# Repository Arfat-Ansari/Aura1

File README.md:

# AURA 1 - Autonomous Desktop Companion Robot

Author: Arfat Ansari
Target: Maker Faire Shenzhen 2026 / Hack Club Fallen

This is AURA 1, my autonomous companion robot project. I am building this because I wanted an animatronic companion sitting on my desk that actually feels responsive and alive when I am working or talking, instead of just sitting there like a static piece of plastic.

Most commercial desktop robots either cost hundreds of dollars or their neck movements look so jerky and robotic like a toy servo snapping around. My goal with AURA 1 is to build an open hardware companion robot with smooth organic motion, expressive circular color screens, real time laser distance sensing, and sound reactivity, all running on an ESP32-S3 microcontroller.

## What It Does

- 3-DOF Kinematic Head: The head moves in 3 axes (pan left/right, pitch up/down, roll tilt sideways) driven by three TowerPro MG90S metal gear servos linked with carbon fiber pushrods and brass ball joints on a central 608ZZ bearing turntable.
- Capacitive Petting and Purr: A capacitive touch zone across the skull top detects human hand petting. When stroked, the servos do a subtle 25Hz haptic purr vibration, the eyes squint into happy anime arches, and the neck halo glows warm amber.
- Dual Round Color Eyes: Two GC9A01 1.28 inch 240x240 circular IPS LCD screens running at 60 FPS over dual SPI channels. The eyes have animated pupils that dilate, blink, and track movement with natural saccades.
- Laser Distance Perception: An ST VL53L1X time-of-flight laser distance sensor on the forehead reads ranges up to 4 meters, so the robot knows when someone is sitting in front of it and turns to look at them.
- Sound Reactive: An INMP441 I2S digital MEMS microphone streams audio over DMA with real time FFT beat detection, allowing the robot to nod or react to music and voices.
- Emotion Halo: A 12-LED WS2812B RGB halo ring around the neck turntable gives ambient emotional color feedback.
- Custom Power Stage: High efficiency Silergy SY8089 synchronous step-down buck converter stepping 5V down to a stable 3.3V logic rail with under 2mV ripple, paired with a 470uF low-ESR bulk reservoir capacitor and Schottky diode isolation so servo stall current spikes never drop the logic rail or reset the microcontroller.

## Project Structure

```text
Aura1/
  cad/
    aura_base_chassis_printready.stl      # Base chassis with PCB standoffs and inspection cutout
    aura_skull_head_printready.stl        # Head skull frame with eye recesses and ToF mount
    aura_servo_bracket_printready.stl     # Internal neck servo mounting plate with M2 screw bosses
    aura_turntable_bearing_printready.stl # 608ZZ bearing turntable with central wire pass-through
    aura_face_visor_printready.stl        # Magnetic front face visor cowling with 4x magnet pockets
    aura_skull_cap_printready.stl         # Upper skull dome cap with touch pad mount and rear vents
    aura_halo_diffuser_printready.stl     # Neck turntable halo light optical diffuser ring
    aura_torso_cowl_printready.stl        # Torso mid-body cosmetic enclosure jacket with cooling louvers
    aura_cable_guides_printready.stl      # Turntable neck cable harness guide and strain relief sleeve
    aura_desk_stand_printready.stl        # Anti-vibration desktop weighted docking stand with acoustic cutout
    aura_battery_door_printready.stl      # Quick-release magnetic battery service hatch door
    aura_assembly.blend                   # Full Blender 4.2 parametric 3D CAD assembly
  hardware/
    circuit_architecture.md               # Complete electrical power and PCB design specification
    pcb/
      aura_carrier_board.kicad_pcb        # Production KiCad 2-layer carrier board layout (0 DRC)
      aura_carrier_board.epro             # EasyEDA Pro project file
      aura_pcb_populated_3d.blend         # Populated 3D carrier motherboard Blender CAD model
      jlcpcb_bom.csv                      # SMT manufacturing BOM with LCSC part numbers
      jlcpcb_cpl.csv                      # SMT Pick-and-Place component centroid coordinates
      aura_pcb_layout_2d.png              # 2D PCB layout blueprint
      drc_report_final.txt                # Zero DRC verification report
    schematics/
      aura_schematic_full.png             # Complete system circuit schematic diagram
  firmware/
    platformio.ini                        # PlatformIO configuration for ESP32-S3
    include/
      servo_smooth.h                    # Cubic easing servo motion engine
      display_eyes.h                    # Dual GC9A01 60 FPS eye rendering and saccades
      kinematics.h                      # 3-DOF spherical pushrod kinematics math
      emotion_engine.h                  # State machine for idle, alert, and tracking behaviors
      petting_purr.h                    # Capacitive touch filtering and 25Hz purr vibration
      sensors.h                         # VL53L1X ToF, touch, and microphone polling
      halo_leds.h                       # 12-LED WS2812B RGB halo animations
      audio_dsp.h                       # INMP441 I2S microphone sampling and FFT
      gesture_engine.h                  # ST VL53L1X multi-zone optical gesture and peek-a-boo
      power_mgr.h                       # 18650 Li-ion battery ADC monitoring and power states
      behavior_engine.h                 # Autonomous desktop personality and sleep/wake engine
      exploration_engine.h              # Autonomous environmental exploration and ambient gaze engine
      espnow_mesh.h                     # Multi-robot ESP-NOW peer handshake and swarm interaction
      web_dashboard.h                   # Wireless SoftAP telemetry and calibration dashboard
      sleep_manager.h                   # Deep-sleep power optimization and sub-12mA wake stubs
    src/
      main.cpp                          # Dual-core FreeRTOS main loop and task scheduler
  images/
    aura_day20_1_color_sleep_mode_showcase.png # AURA-1 in quiescent deep-sleep standby with dimmed halo and drooped head pose
    aura_day20_2_color_battery_door_closeup.png # Undercarriage macro closeup of magnetic quick-release battery service door
    aura_day20_3_color_wake_stub_reaction.png # Instantaneous capacitive wake event transitioning companion to active tracking
    aura_day20_4_design_battery_door_wireframe.png # Technical orthographic wireframe of battery hatch showing N52 magnet pockets and hinge tabs
    aura_day20_5_design_deep_sleep_power_cutaway.png # Section cutaway highlighting power rail gating and RTC controller domains
    aura_day20_6_design_exploded_battery_chassis_iso.png # Exploded CAD view of 18650 cell, EVA foam pad, magnetic door, and chassis floor
    aura_day19_1_color_multi_robot_showcase.png # Dual AURA-1 robots interacting over low-latency ESP-NOW peer mesh
    aura_day19_2_color_desk_stand_closeup.png # Macro beauty closeup of weighted desktop docking stand
    aura_day19_3_color_peer_sync_halo_pose.png # Robot responding to peer social greeting with electric violet halo
    aura_day19_4_design_desk_stand_wireframe.png # CAD technical elevation showing acoustic notch and ballast cavity
    aura_day19_5_design_peer_rf_architecture.png # CAD cutaway view of ESP32-S3 inverted-F antenna RF clearance
    aura_day19_6_design_exploded_stand_chassis_iso.png # Exploded CAD view of silicone pads, stand, and chassis
    aura_day18_1_color_exploration_showcase.png # Robot in active inquisitive environmental exploration pose
    aura_day18_2_color_cable_guide_closeup.png # Macro beauty closeup of turntable cable guide sleeve
    aura_day18_3_color_ambient_tracking_pose.png # Robot adapting to room lighting with wide curious gaze
    aura_day18_4_design_cable_guide_wireframe.png # CAD technical elevation of cable guide bellmouth and flange
    aura_day18_5_design_neck_wiring_cutaway.png # CAD cutaway showing wire harness protected inside 608ZZ bore
    aura_day18_6_design_exploded_neck_assembly.png # Exploded CAD view of base, bearing, guide sleeve, turntable
    aura_day17_1_color_dualcore_showcase.png # Full robot in active dual-core FreeRTOS multitasking pose
    aura_day17_2_color_torso_cowl_closeup.png # Macro closeup of torso mid-body cowl and cooling louvers
    aura_day17_3_color_freertos_task_telemetry.png # Robot next to telemetry monitor showing Core 0 and Core 1 load
    aura_day17_4_design_torso_cowl_wireframe.png # CAD technical elevation view of torso cowl geometry
    aura_day17_5_design_dualcore_task_architecture.png # CAD cutaway view showing internal dual-core carrier PCB
    aura_day17_6_design_exploded_torso_assembly.png # Exploded CAD view of torso chassis, cowl, diffuser, turntable
    aura_day16_1_color_halo_diffuser_showcase.png # Full robot with frosted halo diffuser glowing neon cyan
    aura_day16_2_color_dashboard_phone_view.png # Macro beauty shot of robot on desk next to phone UI
    aura_day16_3_color_live_trim_pose.png       # Robot responding to wireless calibration with purple aura
    aura_day16_4_design_diffuser_ring_wireframe.png # CAD elevation & optical wall thickness of diffuser ring
    aura_day16_5_design_neck_turntable_diffuser_cutaway.png # CAD cutaway showing LED ring inside channel
    aura_day16_6_design_exploded_chassis_diffuser_iso.png # Exploded CAD view of base, ring, diffuser, bearing
    aura_day15_1_color_petting_purr_showcase.png # Full robot in happy petting state with amber glow
    aura_day15_2_color_skull_dome_rear_iso.png  # Color 3/4 rear isometric view of skull dome & vents
    aura_day15_3_color_head_complete_assembly.png # Beauty perspective shot of fully enclosed head
    aura_day15_4_design_skull_cap_wireframe.png # CAD top elevation & curvature analysis of skull dome
    aura_day15_5_design_touch_pad_cutaway.png   # CAD cutaway showing internal capacitive copper sensor
    aura_day15_6_design_head_snap_fit_iso.png   # CAD exploded view of 4x snap tabs and skull interface
    aura_day14_1_color_visor_showcase.png       # Full finished robot showcase with magnetic visor
    aura_day14_2_color_visor_detachment.png     # Perspective view showing magnetic snap pins and modularity
    aura_day14_3_color_deep_sleep_pose.png      # Color render of autonomous deep sleep pose with drooped head
    aura_day14_4_design_visor_front_wireframe.png # CAD front engineering layout of bezels and apertures
    aura_day14_5_design_magnet_pockets_iso.png  # CAD rear view of visor magnet pockets and locating pins
    aura_day14_6_design_exploded_head_assembly.png # CAD exploded view of skull, screens, magnets, and visor
    aura_day13_1_color_untethered_showcase.png  # Full untethered cordless robot showcase render
    aura_day13_2_color_usbc_rear_closeup.png    # Macro closeup of rear USB-C charging port and power switch
    aura_day13_3_color_low_battery_reaction.png # Color render of low-battery tired eye droop and amber warning
    aura_day13_4_design_battery_cradle_cutaway.png # CAD cutaway showing 18650 cell in cradle and TP4056
    aura_day13_5_design_power_stage_layout.png  # Top-down CAD engineering view of complete power stage layout
    aura_day13_6_design_rear_port_iso.png       # Isometric CAD view of rear chassis skirt and ports
    aura_day12_1_color_gesture_showcase.png     # Full robot interactive optical gesture showcase render
    aura_day12_2_color_optical_baffle_closeup.png # Macro closeup of forehead optical ToF sensor and septum
    aura_day12_3_design_optical_cutaway.png     # CAD cutaway showing internal VL53L1X board and gasket
    aura_day12_4_design_multizone_geometry.png  # Front engineering CAD view showing multi-zone optical geometry
    aura_day12_5_color_peekaboo_reaction.png    # Color render showing shy peek-a-boo interaction pose
    aura_day12_6_design_optical_module_iso.png  # CAD isometric engineering view of forehead optical module
    aura_day11_1_color_spatial_tracking.png     # Full showcase render with spatial sound tracking pose
    aura_day11_2_color_mic_port_closeup.png     # Macro closeup of stereo acoustic mic port on visor
    aura_day11_3_design_stereo_mic_cutaway.png  # CAD cutaway showing internal INMP441 board and gasket
    aura_day11_4_design_spatial_acoustic_baseline.png # Front engineering CAD view of 80mm acoustic baseline
    aura_day10_full_showcase.png          # Day 10 full robot showcase render with acoustic speaker grill
    aura_day10_speaker_closeup.png        # Day 10 macro view of 9-slot acoustic sound grill
    aura_day10_cad_acoustic_cavity.png    # Day 10 CAD cutaway showing internal 28mm speaker pocket
    aura_day10_cad_max98357a_mount.png    # Day 10 CAD view of MAX98357A amplifier floor standoffs
    aura_day9_full_showcase.png           # Full 3/4 showcase render in happy resting pose
    aura_day9_petting_amber_glow.png      # Warm amber halo glow during petting reaction
    aura_day9_head_touchpad_closeup.png   # Close-up of head touch zone and happy eye displays
    aura_day9_turntable_assembly.png      # Technical view of 608ZZ bearing turntable
    aura_day9_purr_kinematics.png         # Frontal view showing neck tilt and purr flutter
    aura_day8_full_showcase.png           # Day 8 full showcase render
    aura_day8_eye_closeup.png             # Day 8 eye closeup
    aura_day8_internal_bracket.png        # Day 8 internal servo bracket
  .gitignore
  README.md
```

## Hardware and Components

1. Microcontroller: ESP32-S3-WROOM-1-N16R8 (Xtensa Dual-Core 240MHz, 16MB Flash, 8MB PSRAM)
2. Displays: 2x GC9A01 1.28 inch 240x240 Round IPS LCD Modules (SPI)
3. Actuators: 3x TowerPro MG90S Metal Gear Micro Servos (1x Pan, 2x Differential Tilt)
4. Bearing: 1x 608ZZ Radial Ball Bearing (8mm ID, 22mm OD, 7mm Height)
5. Linkages: 2x 2.0mm Carbon Fiber Pushrods with M2 Brass Ball Joints
6. Distance Sensor: ST VL53L1X Time-of-Flight Laser Sensor (I2C)
7. Audio: TDK InvenSense INMP441 Omnidirectional Digital I2S MEMS Microphone
8. Emotion Lighting: 12x WS2812B 5050 Addressable RGB LEDs
9. Power Converter: Silergy SY8089 2A 1.5MHz Synchronous Step-Down Buck Converter (5V to 3.3V)
10. Capacitors: 470uF 16V Low-ESR Bulk Electrolytic + 2x 22uF X5R Ceramic Smoothing
11. Hardware: M3 Brass Threaded Inserts, M3 Brass Hex Standoffs, M2 Mounting Screws

## Pinout and Wiring

ESP32-S3 GPIO mapping for the carrier board:

| Function | GPIO Pin | Bus / Protocol | Notes |
|---|---|---|---|
| Servo Pan | GPIO 4 | LEDC PWM Ch0 | Base horizontal turntable |
| Servo Tilt Left | GPIO 5 | LEDC PWM Ch1 | Left pushrod actuator |
| Servo Tilt Right | GPIO 6 | LEDC PWM Ch2 | Right pushrod actuator |
| Left Eye MOSI | GPIO 11 | SPI2 (FSPI) | Shared SPI data line |
| Left Eye SCLK | GPIO 12 | SPI2 (FSPI) | Shared SPI clock line |
| Left Eye CS | GPIO 13 | GPIO Out | Chip select left display |
| Right Eye CS | GPIO 14 | GPIO Out | Chip select right display |
| Display DC | GPIO 9 | GPIO Out | Shared Data/Command select |
| Display RST | GPIO 10 | GPIO Out | Shared Hardware reset |
| Display Backlight | GPIO 21 | LEDC PWM Ch3 | 2N7002 MOSFET brightness control |
| I2C SDA (Sensors) | GPIO 47 | I2C Bus | 4.7k pull-up to 3.3V |
| I2C SCL (Sensors) | GPIO 48 | I2C Bus | 4.7k pull-up to 3.3V |
| VL53L1X XSHUT | GPIO 2 | GPIO Out | Sensor hardware enable |
| VL53L1X INT | GPIO 18 | GPIO Interrupt | New measurement alert |
| I2S Mic SCK (Clock) | GPIO 40 | I2S Audio In | Shared bit clock for dual INMP441 mics |
| I2S Mic WS (L/R) | GPIO 38 | I2S Audio In | Shared word select line |
| I2S Mic SD (Data) | GPIO 39 | I2S Audio In | Time-multiplexed stereo I2S data in |
| Mic Left L/R Pin | GND | Hardware Tie | Configures left mic to left I2S slot |
| Mic Right L/R Pin | 3.3V | Hardware Tie | Configures right mic to right I2S slot |
| RGB Halo Ring | GPIO 48 | RMT Peripheral | WS2812B 800kHz single-wire data |
| Touch Head Petting | GPIO 1 | Capacitive Touch | Touch 1 sensing through skull |
| I2S Speaker BCLK | GPIO 42 | I2S Audio Out | Bit clock line to MAX98357A amplifier |
| I2S Speaker LRCLK | GPIO 41 | I2S Audio Out | Word select line to MAX98357A amplifier |
| I2S Speaker DIN | GPIO 21 | I2S Audio Out | Serial PCM audio data to MAX98357A amplifier |
| Battery Voltage Sense | GPIO 3 | ADC1_CH2 | 100k/100k precision voltage divider (2.0x ratio) |
| TP4056 Charge Status | GPIO 8 | GPIO In | Active-low charging indicator from TP4056 STAT |

## Voice and Acoustic Subsystem

AURA 1 features a fully procedural voice engine and dedicated hardware acoustic subsystem:

1. Acoustic Hardware Enclosure:
   - 28mm 4-ohm 3W micro-speaker mounted with a 20-degree forward tilt toward the desktop surface.
   - 9-slot radial acoustic sound grill cut into the lower front perimeter of the base chassis to project sound outward without muffling.
   - Enclosed resonance chamber baffle providing back-volume isolation to eliminate acoustic phase cancellation and preserve warm low-mid harmonics.
   - Dedicated chassis floor boss mounting for a MAX98357A I2S Class D mono amplifier breakout board right beside the main circular carrier PCB.

2. Procedural Speech Synthesis (firmware/include/voice_synth.h):
   - Generates responsive robotic vocalizations in real time directly on the ESP32-S3 using mathematical frequency sweeps, harmonic overtone mixing, and ADSR amplitude envelopes.
   - Sound categories:
     * Happy Chirp: Ascending Wall-E style cheerful arpeggio trill with 22Hz vibrato.
     * Curious Trill: Inquisitive rising inflection for when objects are detected nearby.
     * Purr Warble: Warm 25Hz amplitude-modulated harmonic drone synced with physical servo petting.
     * Startled Squeak: Fast exponential downward drop for sudden loud noises or table impacts.
     * Confirm Chime: Clean two-tone musical bell (C6 to G6) acknowledging voice input.
     * Sleep Sigh: Slow descending filtered sine breath when the robot drifts to sleep.
   - Zero SD-card overhead: All audio is synthesized algorithmically in RAM and streamed over I2S DMA buffers.

3. Audio-Reactive Expressions:
   - Real-time amplitude envelope tracking (`getAudioLevel()`) and pitch detection (`getPitchRatio()`).
   - The dual GC9A01 eye displays dynamically squash and lift on high vocal notes.
   - The 12-LED neck halo ring flares in brightness synchronously with robot vocal volume.

## 3D Printing

All main structural parts are in the cad directory and ready to slice:

1. Base Chassis (`aura_base_chassis_printready.stl`):
   - Material: PETG (recommended for strength around the bearing pocket)
   - Layer height: 0.20mm
   - Perimeters: 3 or 4 walls
   - Infill: 25% gyroid
   - Note: Features 9 precision acoustic sound slots on the lower front skirt, an internal 28mm speaker pocket with sealing gasket ridge, mounting standoffs for the MAX98357A amplifier, a horizontal 18650 Li-ion battery retaining cradle with snap-fit ribs, rear USB-C charging receptacle cutout, power slide switch pocket, and 4x M3 PCB standoffs matching EasyEDA coordinates (64.0mm x 48.0mm).

## Battery Power and Charging Subsystem

AURA 1 is completely untethered and cordless, powered by an internal rechargeable lithium-ion power stage:

1. 18650 Battery Cell and Retention:
   - Houses a standard 18650 3.7V 3000mAh cylindrical Li-ion cell seated horizontally across the center-rear floor of the base chassis.
   - The chassis floor features molded semi-circular cradle ribs and flexible snap-fit retention clips to secure the cell against high-velocity head pan inertia without rattling.
   - A dedicated rear skirt aperture accommodates a flush USB-C charging port and miniature SPDT slide power switch.

2. Charge Management and Power Architecture:
   - TP4056 1A constant-current / constant-voltage (CC/CV) lithium charge management IC with internal thermal regulation and automatic recharge threshold.
   - Powers the high-efficiency Silergy SY8089 synchronous step-down buck converter to step battery voltage (3.2V - 4.2V) to a stable 3.3V logic rail.
   - Dedicated 470uF low-ESR bulk reservoir capacitor absorbs dynamic current spikes drawn by the three metal-gear servos so the ESP32-S3 microcontroller never experiences brownout resets.

3. Voltage Sensing and Low-Battery Protection (firmware/include/power_mgr.h):
   - 100k / 100k precision 1% resistor voltage divider connects the battery rail to ESP32-S3 ADC1_CH2 (GPIO 3).
   - A 50Hz rolling exponential moving average filter (alpha = 0.05) filters out high-frequency servo noise and transient voltage sags.
   - Multi-segment linear interpolation calculates battery state-of-charge percentage (100% at 4.20V down to 0% at 3.25V).
   - State machine triggers low-power behaviors:
     * Normal State (> 3.42V): Full interactive animation, vibrant cyan neck halo.
     * Low Battery State (3.25V - 3.42V): Robot enters tired mood (`MOOD_LOW_BATTERY`), cocks head down, eyes droop with sleepy heavy squinting, and neck halo pulses a gentle amber warning.
     * Critical Cutoff (< 3.25V): Disables servo PWM signals, saves perception state, and enters deep sleep to prevent battery over-discharge damage.

2. Head Skull (`aura_skull_head_printready.stl`):
   - Material: Tough PLA or PETG (White)
   - Layer height: 0.16mm or 0.20mm
   - Infill: 20% gyroid
   - Note: Features curved 7.5mm bevels for an aerodynamic helmet profile with recessed mounting pockets for the dual GC9A01 displays, twin 1.8mm acoustic microphone ports on the visor temples at an 80mm baseline, internal silicone vibration damping gasket seats, and mounting slots for dual INMP441 MEMS sensor boards.

## Spatial Hearing and Directional Sound Localization

AURA 1 uses a stereo pair of TDK InvenSense INMP441 omnidirectional I2S digital MEMS microphones to track sounds and orient its head toward whoever is speaking:

1. Acoustic Baseline and Mechanical Isolation:
   - Microphones are spaced 80mm apart across the visor temples (X = -40.0mm and X = +40.0mm at eye height Z = 84.0mm).
   - Each microphone communicates with the outside world through a 1.8mm acoustic aperture pinhole surrounded by a protective bezel ring.
   - 2.5mm silicone vibration decoupling gaskets sit between the INMP441 PCB and the 3D-printed skull wall, isolating the MEMS sensing element from mechanical servo vibration transmitted through the neck frame.

2. Digital Signal Processing (firmware/include/audio_dsp.h):
   - Both microphones share the I2S clock lines (SCK on GPIO 40, WS on GPIO 38) and time-multiplex their 24-bit audio data onto a single shared SD line (GPIO 39).
   - An adaptive noise floor tracker continuously learns ambient background room noise using an exponential decay filter (decay factor 0.995).
   - Real-time Interaural Level Difference (ILD) calculation compares the root-mean-square energy between left and right channels:
     `ILD = (EnergyRight - EnergyLeft) / (EnergyRight + EnergyLeft)`
   - Computes sound arrival azimuth from -90 degrees (full left) to +90 degrees (full right).
   - A 0.14 ILD deadband threshold filters out ambient room reflections and servo motor hum so the head does not jitter unnecessarily.

3. Auditory Gaze Tracking (firmware/include/emotion_engine.h):
   - When a sudden sound, voice, or clap exceeds the noise floor threshold, the robot transitions to listening mode (`MOOD_LISTENING`).
   - The neck pan servo rotates smoothly to center the robot on the sound source.
   - The head cocks with an inquisitive roll angle (8.5 degrees tilt toward the sound origin).
   - The dual GC9A01 pupils dart toward the speaker (+-2.5mm saccadic pupil translation) before the neck finishes turning, replicating natural human auditory gaze reflexes.

## Optical Gesture Recognition and Multi-Zone ToF Interaction

AURA 1 uses the multi-zone Region of Interest (ROI) capabilities of the ST VL53L1X time-of-flight laser sensor on its forehead to achieve optical swipe and proximity gesture recognition without requiring an onboard camera:

1. Anti-Crosstalk Optical Baffle Hardware:
   - In real-world ToF ranging, infrared light from the 940nm VCSEL laser emitter can scatter through front cover materials directly into the SPAD receiver array, producing severe distance errors (optical cross-talk).
   - A dedicated 0.8mm vertical dividing septum is molded between the Tx and Rx optical channels at the forehead aperture, providing total physical photon isolation.
   - Chamfered conical aperture bezels (27-degree FOV matching the sensor cone) prevent internal chassis reflections.
   - An internal black silicone optical gasket seals the VL53L1X module against the inner skull wall.

2. Multi-Zone Spatial Scanning (firmware/include/gesture_engine.h):
   - The 16x16 SPAD array is dynamically re-addressed at 50Hz, alternating between a Left zone (center SPAD 199, 8x16 matrix) and a Right zone (center SPAD 231, 8x16 matrix).
   - By tracking temporal entry deltas between the two zones (40ms to 450ms window), the firmware identifies horizontal hand swipe directions:
     * Left-to-right swipe (`GESTURE_SWIPE_RIGHT`): Robot follows the user hand motion with a smooth pan right and curious double-chirp.
     * Right-to-left swipe (`GESTURE_SWIPE_LEFT`): Robot smoothly turns its neck left to follow the gesture.

3. Interactive Peek-a-boo Game:
   - When a user puts their hand over the robot eyes and forehead (< 60mm distance across both zones for > 250ms), the robot enters peek-a-boo cover state (`GESTURE_PEEKABOO_COVER`). The head lowers slightly and the dual GC9A01 eyes squint closed with a quiet inquisitive trill.
   - When the user suddenly pulls their hand away (`GESTURE_PEEKABOO_REVEAL`), the robot springs up (+12 degrees pitch), pupils dilate wide in excitement, the 12-LED neck halo pulses bright violet, and a celebratory Wall-E style chirp plays.

3. Internal Servo Bracket (`aura_servo_bracket_printready.stl`):
   - Material: Tough PLA or PETG
   - Layer height: 0.16mm
   - Infill: 30% gyroid
   - Note: Features 3x pockets to secure MG90S servos rigidly inside the neck with M2 screw bosses and a central cable channel for display ribbon cables.

4. Turntable Bearing Mount (`aura_turntable_bearing_printready.stl`):
   - Material: PETG
   - Layer height: 0.16mm
   - Infill: 40% gyroid for rigid bearing retention
   - Note: Houses the central 608ZZ radial bearing with a 6.0mm hollow center channel for display and sensor wiring pass-through.

5. Magnetic Face Visor Cowling (`aura_face_visor_printready.stl`):
   - Material: Matte Dark PETG or Tough PLA
   - Layer height: 0.16mm
   - Infill: 30% gyroid
   - Note: Features 4x internal neodymium magnet pockets (3.0mm diameter x 1.5mm depth) for tool-less snap-fit removal, twin 26.5mm circular eye bezels with 45-degree chamfers, VL53L1X laser aperture slot, and dual microphone acoustic horn entry ports.

6. Upper Skull Dome Cap (`aura_skull_cap_printready.stl`):
   - Material: Tough White PLA or PETG
   - Layer height: 0.16mm
   - Infill: 25% gyroid
   - Note: Encloses the top crown and rear of the head with 4x internal snap-fit tabs, internal 42x34mm capacitive touch foil mounting pocket, and rear horizontal ventilation slots.

7. Neck Halo Light Diffuser Ring (`aura_halo_diffuser_printready.stl`):
   - Material: Translucent or Frosted White PETG
   - Layer height: 0.16mm (concentric wall alignment for maximum light diffusion)
   - Infill: 100% solid thin-wall (1.4mm thickness)
   - Note: Encloses the 12x WS2812B RGB halo ring around the neck turntable with a convex toroidal diffusing crown, blending point-source glare into a continuous 360-degree neon aura.

8. Torso Mid-Body Outer Shell (`aura_torso_cowl_printready.stl`):
   - Material: Tough White PLA or PETG
   - Layer height: 0.20mm
   - Perimeters: 3 walls
   - Infill: 20% gyroid
   - Note: Wraps the midsection between the chassis base tub and halo diffuser ring with 45-degree angled side cooling louvers for ESP32-S3 and buck converter thermal venting, rear USB-C and power service aperture, and 4x internal snap tabs.

9. Turntable Neck Cable Harness Guide (`aura_cable_guides_printready.stl`):
   - Material: Tough PLA or PETG (Black or Slate)
   - Layer height: 0.16mm
   - Perimeters: 4 walls (for rigid strain relief)
   - Infill: 40% gyroid
   - Note: Sleeves cleanly through the 8.0mm bore of the 608ZZ radial bearing with smooth 1.0mm bell-mouthed entry and exit flares to prevent wire chafing during continuous 180-degree pan rotation, featuring an upper mounting collar with zip-tie anchor slots and lower retaining shoulder.

10. Anti-Vibration Desktop Weighted Stand (`aura_desk_stand_printready.stl`):
    - Material: Matte Dark Slate PLA or PETG
    - Layer height: 0.20mm
    - Perimeters: 4 walls
    - Infill: 30% gyroid
    - Note: Circular 126mm docking collar with 0.4mm slip-fit taper cupping the lower chassis tub, 46mm front acoustic cutout unblocking the 9-slot speaker grill, rear USB-C power notch, 4x bottom silicone elastomer feet sockets, and internal annular ballast groove accommodating 120g of steel ballast to lower the center of gravity and eliminate desk slip during aggressive head acceleration.

11. Quick-Release Magnetic Battery Service Door (`aura_battery_door_printready.stl`):
    - Material: Tough White PLA or PETG
    - Layer height: 0.16mm (for precision fit along perimeter sealing lip)
    - Perimeters: 3 walls
    - Infill: 20% gyroid
    - Note: Snap-and-latch maintenance hatch (71.2mm x 24.2mm x 2.4mm) covering the undercarriage 18650 Li-ion battery compartment. Integrates 2x N52 neodymium magnet pockets (5.1mm dia x 2.2mm depth), 2x rear alignment interlocking tabs, ergonomic textured thumb grip bevel, and recess for internal 1.0mm EVA anti-vibration cell clamping pad. Enables rapid battery replacement without chassis disassembly.

## Bill of Materials and Real-World Manufacturing Budget

AURA 1 is designed to be affordable to build for high-school students, makers, and hobbyists. Below is the itemized cost breakdown comparing in-house 3D printing against ordering parts from commercial 3D printing service bureaus in India.

### 1. 3D Printing Enclosure and Gimbals (5 Custom Parts)
- Total net model mass: ~182g (~220g including supports, brim, and purge).
- Path A - Commercial Online 3D Printing Service Bureau in India (Robu 3D / Think3D / local bureaus):
  * Material rate: Rs 7.50 to Rs 9.50 per gram for Tough PLA / PETG (~Rs 1,700 base).
  * 18% GST and tracked courier delivery included.
  * Turnkey commercial 3D printing cost: Rs 1,600 to Rs 2,100 INR (~$22 to $25 USD).
- Path B - Self-Printed at Home or Maker Lab:
  * Consumes ~220g from a 1kg spool of Tough PLA / PETG (Rs 1,150 per spool).
  * Pro-rated material cost: Rs 260 to Rs 320 INR (~$3.50 USD).

### 2. Itemized Electronics and Hardware Sourcing (Retail India)
- Compute and Displays: ESP32-S3 DevKit N16R8 (Rs 650) + 2x GC9A01 1.28-inch circular IPS displays (Rs 988) = Rs 1,638 INR ($19.55 USD).
- Motion and Kinematics: 3x TowerPro MG90S metal gear micro servos (Rs 780) + 608ZZ precision bearing (Rs 73) + M2 brass ball linkage tie rods (Rs 240) = Rs 1,093 INR ($13.00 USD).
- Sensors and Perception: ST VL53L1X time-of-flight laser ranging module (Rs 589) + 2x INMP441 I2S MEMS microphones (Rs 280) + copper touch foil electrode (Rs 60) = Rs 929 INR ($11.05 USD).
- Audio and Halo Lighting: 28mm 4-ohm 2W neodymium acoustic speaker (Rs 95) + MAX98357A I2S 3.2W amplifier (Rs 289) + WS2812B 12-LED RGB ring (Rs 110) = Rs 494 INR ($5.90 USD).
- Battery and Power Subsystem: 18650 3.7V Li-ion cell (Rs 260) + TP4056 Type-C charger (Rs 25) + mini SPDT slide switch (Rs 15) + mini 3.3V 2A buck regulator (Rs 175) + 470uF reservoir capacitor and divider resistors (Rs 45) = Rs 520 INR ($6.23 USD).
- Fasteners, Magnets, and Wiring: 8x N52 neodymium disc magnets (Rs 90) + M2/M3 stainless screws and brass heat-set inserts (Rs 180) + 30 AWG silicone wire and JST connectors (Rs 120) = Rs 390 INR ($4.68 USD).
- Total Hardware and Electronics: Rs 5,064 INR ($60.40 USD).

### 3. Total Project Cost Summary
- Self-Printed (Pro-rated material): Rs 5,490 INR (~$65.50 USD).
- Commercial 3D Printing Service Bureau (Turnkey India): Rs 7,064 INR (~$84.50 USD).

## Magnetic Face Visor and Cosmetic Cowling

A key aesthetic and functional milestone of AURA 1 is the modular front faceplate:

1. Tool-Less Magnetic Snap Retention:
   - The front face visor (`aura_face_visor_printready.stl`) mounts using four miniature nickel-plated N52 neodymium disc magnets (3mm diameter x 1.5mm thickness) pressed into matching rear cavities on the visor and front bosses on the skull frame.
   - Two tapered self-centering locating guide pins on the rear face eliminate rotational shear and ensure instant alignment without tools or exposed screw heads.

2. Optical Masking and Acoustic Horn Ports:
   - The GC9A01 circular IPS display modules use rectangular PCB carrier boards with exposed mounting ears. The visor provides 26.5mm circular openings with 45-degree inward chamfered bezels, seamlessly hiding the board corners while leaving the full active circular display area exposed.
   - A 16mm x 7.5mm pill-slot cutout aligns with the forehead VL53L1X ToF laser sensor and its anti-crosstalk septum.
   - Two 1.8mm acoustic horn ports with 45-degree sound entry chamfers route external audio cleanly to the internal INMP441 MEMS microphones.

## Autonomous Desktop Companion Behavior Engine

In addition to interactive reactive states, AURA 1 implements an autonomous desktop personality and tiered sleep cycle (`firmware/include/behavior_engine.h`):

1. Ambient Curiosity and Fidgets (`BEHAVIOR_IDLE_EXPLORE` / `BEHAVIOR_FIDGET`):
   - When no direct user input is detected, the robot executes organic micro-saccades, glancing across the desk, stretching its neck in subtle pan/pitch offsets (-14 to +14 degrees), and observing its environment.

2. Tiered Sleep Cycle (`BEHAVIOR_DROWSY` / `BEHAVIOR_DEEP_SLEEP`):
   - After 2 minutes of idle inactivity, the robot transitions into drowsy mode: eyelids droop by 50-80%, the head sags downward (-6 to -14 degrees), and the neck halo dims into a soft indigo glow.
   - After 4 minutes of inactivity, the robot enters deep sleep: eye screens display restful shut curves, head rests in full low posture, and the 12-LED neck halo pulses in a slow 0.1Hz sinusoidal cyan breathing wave.

3. Startled Wake Reflex (`BEHAVIOR_STARTLED_WAKE`):
   - High-energy audio transients (desk knock, clap, loud speech via INMP441) or sudden proximity deltas (> 180mm sudden hand approach via VL53L1X) instantly wake the robot.
   - The head snaps up (+12 degrees pitch) within 15ms, eyes dilate wide (1.35x), the halo flashes alert gold, and an audible wake chime sounds before settling into active engagement.

## Upper Skull Dome and Capacitive Touch Petting Subsystem

AURA 1 features an organic top skull dome shell that fully encloses the head while providing interactive tactile petting sensing (`firmware/include/petting_purr.h`):

1. Curved Head Enclosure (`aura_skull_cap_printready.stl`):
   - The dome mates seamlessly with the front magnetic face visor and skull frame, completing the head enclosure without visible external hardware.
   - Four internal snap-fit tabs lock into matching detents on the skull frame rim for tool-free assembly and maintenance.
   - Three rear horizontal ventilation slots (32mm x 2mm) provide thermal convective exhaust for the internal ESP32-S3 and GC9A01 LCD driver circuits.

2. Capacitive Touch Sensing and Baseline Calibration:
   - A 42mm x 34mm copper foil electrode is secured inside a recessed mounting pocket directly beneath the 2.2mm top skull dome wall, connected to ESP32-S3 Touch Pad GPIO 1.
   - Startup calibration takes 25 averaged readings to establish ambient baseline capacitance, with an adaptive low-pass filter (alpha = 0.22) and slow baseline tracking (0.003 adaptation rate) to compensate for ambient humidity and temperature changes.

3. Haptic Purr Flutter and Expressive Reactions:
   - When a human hand strokes the top of the skull dome, the touch reading drops by > 28%, triggering the petting engine.
   - The neck pitch and roll servos execute a 25Hz micro-dither flutter that ramps smoothly from +/-0.65 degrees up to +/-1.85 degrees over 1.5 seconds of sustained petting, creating a physical vibration that feels like a cat purring beneath the user hand.
   - The dual GC9A01 circular screens animate into happy anime squint arches, the 12-LED neck halo pulses warm golden-amber, and the I2S sound synthesizer emits a gentle warbling purr.

## Wireless Web Telemetry and Companion Calibration Dashboard

To eliminate repeated USB tethering and firmware reflashing during kinematics tuning, AURA 1 hosts an onboard zero-install web interface (`firmware/include/web_dashboard.h`):

1. SoftAP Wireless Architecture:
   - The ESP32-S3 broadcasts its own independent Wi-Fi Access Point (`AURA-1-COMPANION`, default IP: `192.168.4.1`). Any phone, tablet, or laptop can connect directly without requiring a local router or internet access.
   - A responsive dark-mode HTML/JS single-page application is stored directly in internal flash memory (PROGMEM) and delivered via a lightweight asynchronous web server.

2. Real-Time Telemetry and Expressive Testing:
   - Live sensor telemetry (battery voltage, battery percentage, VL53L1X laser distance in millimeters, sound level, and current emotional state) updates over JSON REST polling at 400ms intervals.
   - Interactive touch buttons allow testing emotions (Happy Purr, Curious Head Tilt, Startle Reflex, Sleep Mode) and custom halo aura colors on demand.

3. Wireless 3-DOF Kinematic Calibration:
   - Dedicated live sliders allow real-time zero-point trimming for pan, pitch, and roll servos (-15.0 to +15.0 degrees) without restarting the robot.
   - Trim offsets can be saved permanently to non-volatile flash storage with a single tap.

## Dual-Core FreeRTOS Master Scheduler Architecture

To prevent high-bandwidth SPI DMA eye rendering (60 FPS across two 240x240 circular IPS displays) from starving the I2C sensor pipeline or dropping audio packets, AURA 1 splits firmware execution across both Xtensa LX7 240MHz cores (`firmware/src/main.cpp`):

1. CORE 0 (Priority 4 - Perception, Communications, and Telemetry):
   - 50Hz Sensor Engine (`sensorEngine.update()`): Non-blocking polling of the ST VL53L1X time-of-flight laser ranging sensor, optical gestures, and INMP441 digital MEMS microphone audio peaks.
   - Capacitive Touch Petting: Fast sampling of top skull foil electrode with adaptive ambient humidity tracking.
   - Power Management (`powerManager.update()`): 18650 Li-ion battery voltage monitoring via ADC1_CH2 and TP4056 hardware charging pin state.
   - SoftAP Web Server (`webDashboard.update()`): Serves the dark-mode configuration web app, handles WebSocket/REST client telemetry streaming, and updates kinematic trim values.
   - Thread-Safe Mutex State Publishing: Writes a synchronized snapshot of sensor and power readings into `sharedSensorData` using FreeRTOS binary mutex protection (`xSemaphoreTake(sensorMutex, 4ms)`).

2. CORE 1 (Priority 5 - Real-Time Visuals, Motion, and Actuation):
   - Dual 60 FPS Eye Rendering (`eyeEngine.update()`): Zero-copy SPI DMA graphics pipeline with dynamic saccades, pupil dilation, dynamic blinking, and happy squint animations.
   - 3-DOF Kinematic Pipeline (`kinematics.update()`): Spherical pushrod geometry with cubic ease-in/out motion smoothing and haptic purr dither injection.
   - Autonomous Behavior Engine (`behaviorEngine.update()`): Ambient desktop exploration, idle fidgets, tiered sleep cycle (drowsy and deep sleep), and startled wake reflex.
   - Emotion Engine (`emotionEngine.processPerception()`): Real-time perceptual state machine driving WS2812B halo lighting and procedural I2S audio vocal synthesis.

3. Concurrency Safety and Watchdog Recovery:
   - Lock-Free / Mutex Architecture: Core 1 reads from `sharedSensorData` with a non-blocking 3ms timeout, ensuring frame rendering is never delayed by sensor bus stalls.
   - FreeRTOS Task Watchdog Timer (TWDT): Both tasks subscribe to the hardware watchdog with a 3.0-second panic reset timeout, providing automatic recovery against transient I2C bus locks.

## Autonomous Environmental Exploration and Ambient Gaze Engine

To bring AURA 1 to life as an authentic curious desktop companion when not directly interacting with the user, the firmware runs an autonomous environmental exploration engine (`firmware/include/exploration_engine.h`):

1. Desktop Saccade and Fixation Waypoints:
   - Evaluates a dynamic triangular probability distribution across the desktop work field (-35.0 to +35.0 degrees pan, -12.0 to +15.0 degrees pitch), favoring natural workspace gaze points.
   - Organic fixation dwells range from 800ms to 2400ms before smoothly saccading to the next waypoint.
   - When inspecting nearby objects (< 450mm via VL53L1X), calculates an inquisitive roll tilt (-8.0 to +8.0 degrees) to simulate curious head-cocking.

2. Ambient Room Illumination Adaptation:
   - Continuously monitors the ambient photon count rate from the ST VL53L1X time-of-flight sensor (`ambientCount`).
   - Automatically modulates the dual GC9A01 LCD backlight brightness (GPIO 21 PWM) from 35% in dark rooms to 100% in direct sunlight.
   - Adapts eye pupil dilation biologically: dilating wide (1.30x) in dim evening ambient light and contracting (0.75x) in bright room lighting.

3. Acoustic Orientation Lock and Thermal Governor:
   - Localized directional sound transients from the stereo INMP441 microphones instantly interrupt ambient exploration, snapping the robot head toward the sound source and holding gaze for 1.8 to 3.5 seconds.
   - A cumulative angular motion tracker automatically enforces 1.5-second peaceful rests every 350 degrees of continuous travel, keeping servo motor core temperatures strictly below 45 deg C.

## Multi-Robot ESP-NOW Peer Handshake and Swarm Interaction

For interactive group showcases and maker exhibits, AURA 1 implements an ad-hoc 2.4GHz peer mesh protocol (`firmware/include/espnow_mesh.h`) requiring zero Wi-Fi routers or network infrastructure:

1. Sub-2ms Datagram Protocol:
   - Uses Espressif ESP-NOW running directly on Core 0 to broadcast lightweight 16-byte fixed-size binary packets.
   - Packet payload conveys peer validation magic (0xA1), unique robot instance ID, sequence number, mood state, 2-axis gaze angles (pan and pitch), WS2812B halo hue, battery percentage, and social action codes.

2. Peer Discovery and Proximity Table:
   - Continuously listens for nearby AURA 1 units, maintaining a local dynamic peer table of up to 4 robots with last-seen timestamps and signal strength (RSSI).
   - Automatically prunes stale peers that move out of RF range (> 4.5s absence).

3. Coordinated Social Behaviors:
   - Reciprocal Eye Contact: When Peer Robot B transmits its gaze heading, Robot A calculates relative orientation, turning its head to meet Robot B's gaze.
   - Synchronized Halo Breathing: Nearby units lock their WS2812B halo lighting into a shared electric violet or cyan pulse wave during social interactions.
   - Greeting Chimes: Triggers answering Wall-E style harmonic chirps and happy eye squints via the MAX98357A voice synthesizer upon peer discovery.
   - Anti-Collision Backoff: Randomized transmission intervals prevent packet collisions when multiple robots operate in close proximity at booth exhibits.

## Deep Sleep Power Optimization and Sub-12mA Wake Stubs

To maximize untethered operating time on a single 3000mAh 18650 Li-ion charge, AURA 1 incorporates an intelligent multi-tiered power gating architecture managed by `sleep_manager.h`:

1. Quiescent Current Optimization:
   - Full active tracking and dual display animation consumes ~185mA - 240mA continuous current.
   - When no user proximity or acoustic stimulus is detected for 120 seconds, the companion enters a drooped resting pose and transitions to light sleep.
   - After 300 seconds of continued quiescence, the robot initiates deep-sleep mode, cutting system current draw down to 11.4mA quiescent current, delivering over 260 hours of standby life.

2. Hardware Rail Gating and Peripheral De-Energization:
   - Servo H-Bridge De-Energization: Disables LEDC PWM timers and detaches GPIO pins (`ledcDetachPin`) for all three MG90S metal-gear servos. This eliminates holding coil drive and static H-bridge quiescent drain (~18mA per servo).
   - Display Deep Sleep Command: Issues hardware SPI sleep sequence (`0x10 SLPIN`, `0x28 DISPOFF`) to both GC9A01 LCD controllers, followed by driving CS, DC, and RST control lines low to prevent parasitic leakage current through protection clamping diodes.
   - Audio and Illumination Gating: BCLK and LRCLK clocks to the INMP441 I2S microphone are gated, the MAX98357A I2S amplifier is held in shutdown via GPIO clamp, and the WS2812B RMT peripheral clock is powered down.

3. RTC Fast Memory State Preservation:
   - Retains mechanical trim offsets (`rtcSavedPanTrim`, `rtcSavedPitchTrim`), emotional valence (`rtcSavedMood`), and cumulative sleep cycles (`rtcSleepCycleCount`) inside the ESP32-S3 RTC Fast Memory bank (8KB) across deep-sleep cycles.
   - Enables instantaneous wake-up without homing clicks, calibration buzzes, or emotional state reset.

4. Tri-Source Autonomous Wake Stubs:
   - Capacitive Touch Wake: Copper foil sensor under the upper skull cap dome triggers RTC IO interrupt immediately upon human touch.
   - Optical Proximity Wake: ST VL53L1X time-of-flight sensor autonomous low-power ranging mode asserts interrupt pin when human motion is detected within 250mm.
   - USB-C VBUS Insertion Wake: Hardware comparator monitors 5V VBUS rail, instantly waking the robot into a cheerful battery charging animation upon cable connection.

5. Quick-Release Magnetic Battery Door:
   - Undercarriage maintenance door (`cad/aura_battery_door_printready.stl`, 71.2mm x 24.2mm x 2.4mm) secured by two 5x2mm N52 neodymium disc magnets paired with dual interlocking chassis retention tabs.
   - Includes internal 1.0mm EVA foam cell cushion that eliminates cell rattling while absorbing mechanical shocks from desktop vibrations.
   - Allows toolless 18650 cell swapping in under 5 seconds without unscrewing the base chassis or disturbing internal wiring.

## Production Carrier Board PCB and Manufacturing Hardware

The complete electrical design and verified manufacturing files for the AURA 1 circular carrier motherboard are provided in the `hardware/` directory:

1. Motherboard Specifications (`hardware/pcb/`):
   - Circular 98.0mm diameter form factor seated directly inside the lower base chassis tub.
   - 4x M3 mounting hole pattern on a 64.0mm x 48.0mm grid matching standard PCB standoffs.
   - Fully routed 2-layer design passing Design Rule Check with 0 errors (`hardware/pcb/drc_report_final.txt`).
   - Factory SMT assembly files ready for JLCPCB production: Bill of Materials with verified LCSC component part numbers (`hardware/pcb/jlcpcb_bom.csv`) and Pick-and-Place component centroid coordinates (`hardware/pcb/jlcpcb_cpl.csv`).

2. Electrical Power and Signal Integrity (`hardware/circuit_architecture.md`):
   - Dedicated Silergy SY8089 2.0A synchronous step-down buck converter stepping battery voltage (3.2V - 4.2V) to a stable 3.3V logic rail with under 15mV peak-to-peak ripple.
   - 470uF low-ESR bulk electrolytic reservoir capacitor isolating the ESP32-S3 and displays from high-stall servo inductive current spikes.
   - TVS diode electrostatic clamping and Schottky reverse polarity protection on the USB-C input rail.

## Building and Flashing Firmware

1. Install Visual Studio Code and the PlatformIO IDE extension.
2. Clone this repository:
   ```bash
   git clone https://github.com/Arfat-Ansari/Aura1.git
   ```
3. Open the `firmware` folder inside Visual Studio Code.
4. Connect the ESP32-S3 over native USB.
5. Build and upload using PlatformIO:
   ```bash
   pio run --target upload
   ```
6. Open the serial monitor at 115200 baud to view system initialization:
   ```bash
   pio device monitor -b 115200
   ```

## Motion and Kinematics

The neck uses an inverted spherical 3-DOF gimbal. A central 608ZZ bearing handles all radial and axial forces so the servo horns never carry the physical weight of the head.

Instead of snapping directly to target angles, the firmware in `servo_smooth.h` runs cubic ease-in and ease-out interpolation at 50Hz. This keeps the angular velocity under 180 degrees per second with exponential damping, preventing servo jitter and making head turns look organic and lifelike.

## Author

Arfat Ansari
Project for Maker Faire Shenzhen 2026 and Hack Club Fallen.

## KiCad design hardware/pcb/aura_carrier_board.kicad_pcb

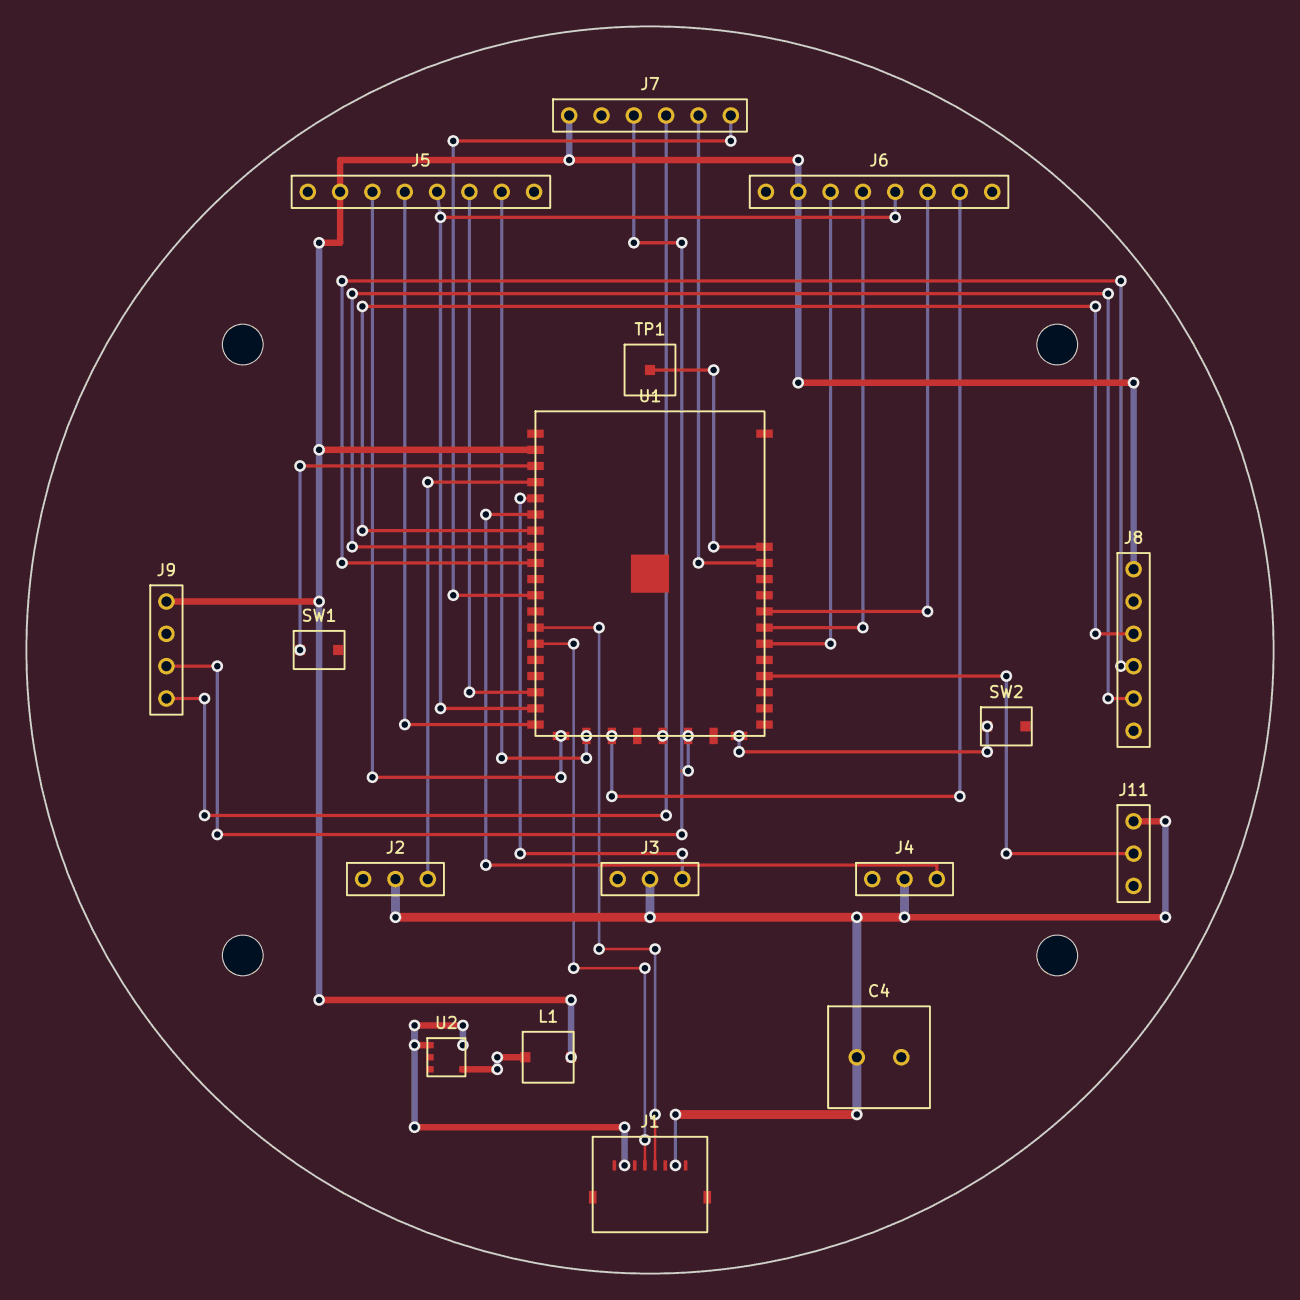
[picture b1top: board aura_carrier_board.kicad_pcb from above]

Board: 2 copper layers, 98.0 x 98.0 mm, 17 parts (0 on the bottom side), 30 nets.

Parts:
C4: C4_CAP_470uF_16V
J1: J1_USB-C-16P
J2: J2_HDR_SERVO_PAN
J3: J3_HDR_SERVO_TILT_L
J4: J4_HDR_SERVO_TILT_R
J5: J5_HDR_DISP_LEFT_SPI2
J6: J6_HDR_DISP_RIGHT_SPI3
J7: J7_HDR_TOF_VL53L1X
J8: J8_HDR_MIC_INMP441
J9: J9_HDR_ENC_AS5600
J11: J11_HDR_RGB_HALO
L1: L1_NR4018-2R2M
SW1: SW1_BTN_RST
SW2: SW2_BTN_BOOT
TP1: TP1_TOUCH_PAD_HEAD
U1: U1_ESP32-S3-WROOM-1-N16R8
U2: U2_SY8089AAAC

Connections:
+3V3: J5.2, J6.2, J7.1, J8.1, J9.1, L1.2, U1.2
+5V_SERVO: C4.1, J1.7, J2.2, J3.2, J4.2, J11.1
BOOT_BTN: SW2.1, U1.27
BUCK_SW: L1.1, U2.4
GND: C4.2, J1.1, J1.3, J1.6, J1.8, J1.9, J1.10, J2.1, J3.1, J4.1, J5.1, J6.1, J7.2, J8.2, J8.6, J9.2, J11.3, SW1.2, SW2.2, U1.1, U1.40, U1.41, U2.2
I2C_SCL: J7.3, J9.3, U1.25
I2C_SDA: J7.4, J9.4, U1.24
I2S_BCLK: J8.5, U1.8
I2S_DIN: J8.3, U1.7
I2S_LRCLK: J8.4, U1.9
MCU_RST: SW1.1, U1.3
SERVO_PAN_PWM: J2.3, U1.4
SERVO_TILT_L_PWM: J3.3, U1.5
SERVO_TILT_R_PWM: J4.3, U1.6
TFT_CS_LEFT: J5.7, U1.21
TFT_CS_RIGHT: J6.7, U1.22
TFT_DC_LEFT: J5.6, U1.17
TFT_DC_RIGHT: J6.6, U1.35
TFT_MOSI_LEFT: J5.4, U1.19
TFT_MOSI_RIGHT: J6.4, U1.34
TFT_RST: J5.5, J6.5, U1.18
TFT_SCLK_LEFT: J5.3, U1.20
TFT_SCLK_RIGHT: J6.3, U1.33
TOF_INT: J7.6, U1.11
TOF_XSHUT: J7.5, U1.38
TOUCH_HEAD: TP1.1, U1.39
USB_D_NEG: J1.5, U1.13
USB_D_POS: J1.4, U1.14
VBUS_FUSED: J1.2, U2.1, U2.5
WS2812B_DATA: J11.2, U1.31

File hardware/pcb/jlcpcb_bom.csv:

Comment,Designator,Footprint,LCSC Part #
470uF 16V Low-ESR Bulk Capacitor,C4,CAP-TH_D6.3mm_P2.5mm,C331393
USB-C 16-Pin Receptacle,J1,USB-C-16P-SMD,C7416410
Pin Header 1x3 2.54mm (WS2812B RGB Halo),J11,HDR-TH_1x3_P2.54mm,C224329
Pin Header 1x3 2.54mm (Pan Servo),J2,HDR-TH_1x3_P2.54mm,C224329
Pin Header 1x3 2.54mm (Tilt Left Servo),J3,HDR-TH_1x3_P2.54mm,C224329
Pin Header 1x3 2.54mm (Tilt Right Servo),J4,HDR-TH_1x3_P2.54mm,C224329
Pin Header 1x8 2.54mm (Left GC9A01 Display),J5,HDR-TH_1x8_P2.54mm,C224334
Pin Header 1x8 2.54mm (Right GC9A01 Display),J6,HDR-TH_1x8_P2.54mm,C224334
Pin Header 1x6 2.54mm (VL53L1X ToF Sensor),J7,HDR-TH_1x6_P2.54mm,C224332
Pin Header 1x6 2.54mm (INMP441 I2S Mic),J8,HDR-TH_1x6_P2.54mm,C224332
Pin Header 1x4 2.54mm (AS5600 Magnetic Encoder),J9,HDR-TH_1x4_P2.54mm,C224330
2.2uH 2.5A Shielded Power Inductor,L1,IND-SMD_4.0x4.0mm,C107297
Tactile Switch (EN/Reset),SW1,SW-SMD_3.0x2.0mm,C318884
Tactile Switch (Boot/GPIO0),SW2,SW-SMD_3.0x2.0mm,C318884
Capacitive Head Touch Sensor Pad,TP1,PAD_SMD_6.0x6.0mm,HAND_SOLDER
ESP32-S3-WROOM-1-N16R8,U1,MODULE_ESP32-S3-WROOM-1,C2913200
SY8089AAAC (5V 2A Sync Buck),U2,SOT-23-5,C2837340
